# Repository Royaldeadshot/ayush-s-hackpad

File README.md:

# **Hackpad — Volume + Macro Controller**

##### This is my custom hackpad built for Hack Club Blueprint.

##### It’s a small under-desk controller that lets me:

* ###### Control volume with a rotary encoder

###### 

* ###### Play / pause with encoder press

###### 

* ###### Use shortcut keys (Chrome, Copy, Paste, LED mode)

###### 

* ###### Show animations + volume on an OLED

###### 

* ###### Control RGB effects with presets using one of the keys

###### I designed the PCB in KiCad, modeled the case in Fusion, and programmed it using KMK.

### **🖼️ Screenshots**

###### 

* #### Overall Hackpad

#### 

* #### Schematic

#### 

* #### PCB Layout

#### 

* #### Case + How It Fits Together

###### 

###### 

## ***🧩 Features***

###### 

* #### 4 mechanical keys

#### 

* #### EC11 rotary encoder with push

#### 

* #### SSD1306 0.91" OLED (128×32)

#### 

* #### 8x SK6812 RGB LEDs (underglow)

#### 

* #### USB HID (macros + media control)

#### 

* #### Animation when idle, volume overlay when adjusting

#### 

* #### LED presets controlled by a key

###### 

## ***🧾 Parts List***

#### **Part				                  Quantity		   Notes**

#### Seeed XIAO RP2040		             1			     Main controller

#### MX mechanical switches		         4			     With keycaps

#### EC11 rotary encoder		           1			     With push button

#### SSD1306 OLED, 0.91", 4-pin	       1			     I2C (GND-VCC-SCL-SDA)

#### SK6812 MINI-E LEDs		             8			     Addressable RGB

#### 330Ω resistor			               1			     LED data line

#### 1000µF capacitor		               1			     Across 5V + GND near LEDs

#### 1N4148 diodes			               4			     One per switch

#### M3 heat-set inserts		           2		       For mounting

#### M3×16mm screws	                   2           For PCB mounting

#### 3D printed case + plate	         1	         Custom Fusion design

## **⚙️ Firmware**

###### 

##### **Framework: KMK**

###### 

### **Functions:**

###### 

##### Volume up/down (encoder)

##### 

##### Play / pause (encoder press)

##### 

##### Chrome launch

##### 

##### Copy / Paste

##### 

##### LED mode toggle

##### 

##### Idle animation resumes after volume change

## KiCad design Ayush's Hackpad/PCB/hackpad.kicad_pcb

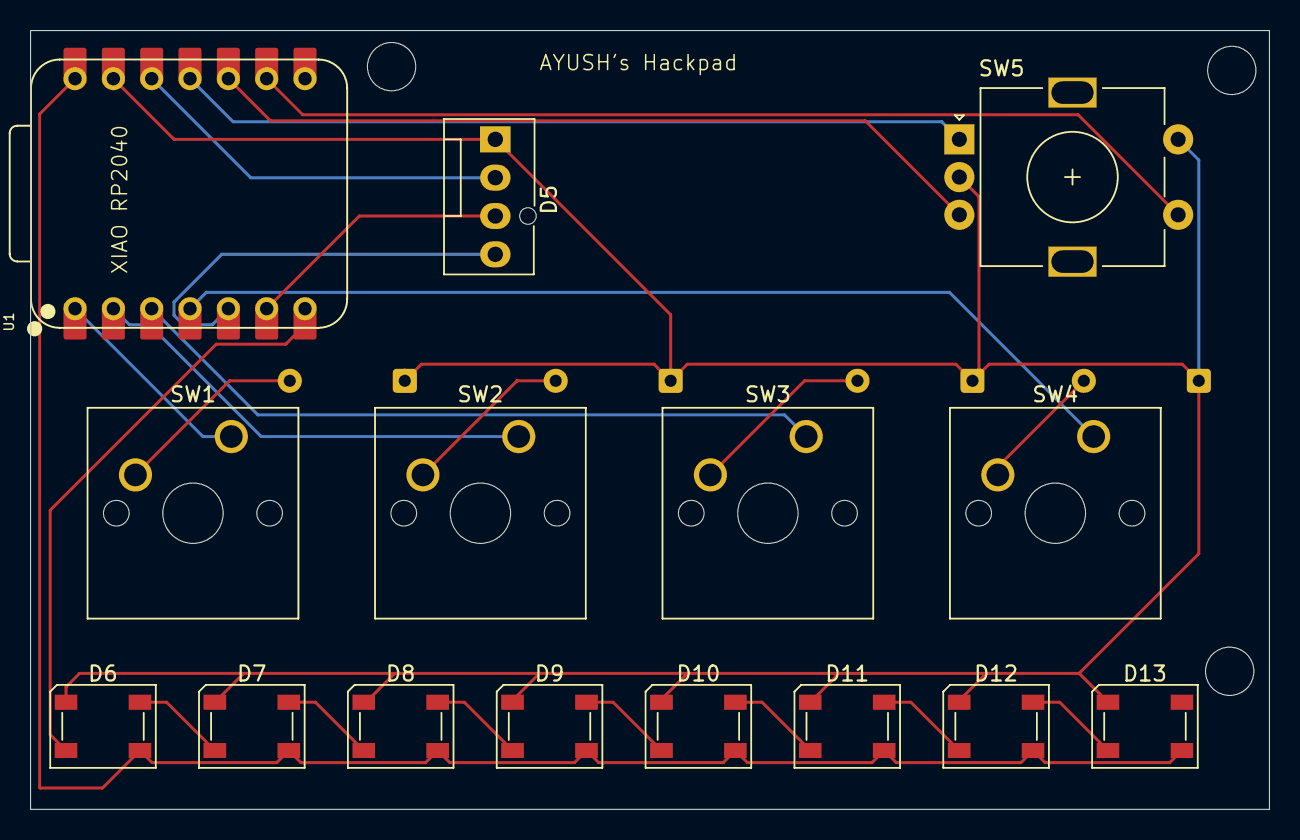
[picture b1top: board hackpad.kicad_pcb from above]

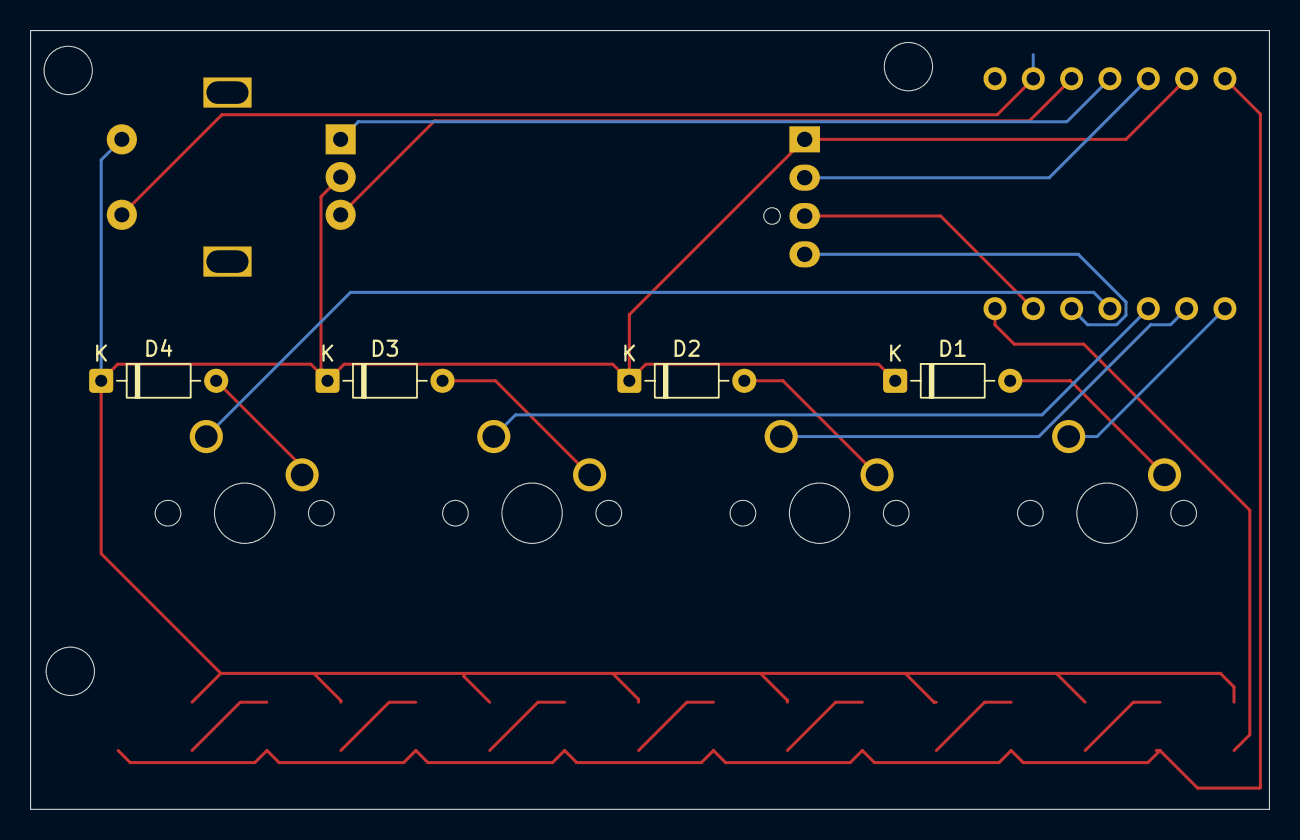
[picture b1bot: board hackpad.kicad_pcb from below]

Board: 2 copper layers, 82.1 x 51.6 mm, 19 parts (4 on the bottom side), 24 nets.

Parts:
D1, D2, D3, D4: 1N4148; D_DO-35_SOD27_P7.62mm_Horizontal
D5: OLED_0.91_I2C; FanPinHeader_1x04_P2.54mm_Vertical
D6, D7, D8, D9, D10, D11, D12, D13: SK6812; LED_SK6812_PLCC4_5.0x5.0mm_P3.2mm
SW1, SW2, SW3, SW4: SW_Push; SW_Cherry_MX_1.00u_PCB
SW5: RotaryEncoder_Switch; RotaryEncoder_Alps_EC11E-Switch_Vertical_H20mm
U1: XIAO-RP2040-DIP

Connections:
+3.3V: D5.2 (VCC), U1.12 (3V3)
+5V: D6.3 (VDD), D7.3 (VDD), D8.3 (VDD), D9.3 (VDD), D10.3 (VDD), D11.3 (VDD), D12.3 (VDD), D13.3 (VDD), U1.14 (VBUS)
GND: D1.1 (K), D2.1 (K), D3.1 (K), D4.1 (K), D5.1 (GND), D6.1 (VSS), D7.1 (VSS), D8.1 (VSS), D9.1 (VSS), D10.1 (VSS), D11.1 (VSS), D12.1 (VSS), D13.1 (VSS), SW5.C, SW5.S2, U1.13 (GND)
unnamed: D1.2 (A), SW1.2
unnamed: D2.2 (A), SW2.2
unnamed: D3.2 (A), SW3.2
unnamed: D4.2 (A), SW4.2
unnamed: D5.3 (SCL), U1.6 (GPIO7/SCL)
unnamed: D5.4 (SDA), U1.5 (GPIO6/SDA)
unnamed: D6.2 (DIN), U1.7 (GPIO0/TX)
unnamed: D6.4 (DOUT), D7.2 (DIN)
unnamed: D7.4 (DOUT), D8.2 (DIN)
unnamed: D8.4 (DOUT), D9.2 (DIN)
unnamed: D9.4 (DOUT), D10.2 (DIN)
unnamed: D10.4 (DOUT), D11.2 (DIN)
unnamed: D11.4 (DOUT), D12.2 (DIN)
unnamed: D12.4 (DOUT), D13.2 (DIN)
unnamed: SW5.S1, U1.9 (GPIO2/SCK)
unnamed: SW5.A, U1.11 (GPIO3/MOSI)
unnamed: SW5.B, U1.10 (GPIO4/MISO)
unnamed: SW1.1, U1.1 (GPIO26/ADC0/A0)
unnamed: SW2.1, U1.2 (GPIO27/ADC1/A1)
unnamed: SW3.1, U1.3 (GPIO28/ADC2/A2)
unnamed: SW4.1, U1.4 (GPIO29/ADC3/A3)
